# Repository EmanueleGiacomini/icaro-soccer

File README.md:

# Icaro Soccer
Questo repository contiene tutti i dati riguardo alla progettazione di hardware e software per i robot calciatori sviluppati nel corso **Icaro** tenuto nell'instituto tecnico industriale **Pacinotti-Archimede** di Roma.

## Struttura repository
Entrambe le sottocartelle di software e hardware contengono una cartella **_reference_** contenente ideè e link utili per la progettazione.
### Software
Ogni sottocartella è composta da un file di estensione **ino** che contiene il programma da inserire in Arduino, e da una cartella
**src** che contiene le librerie utilizzate dal programma.

Le librerie presenti sono:<p>
-**comlib** : libreria che gestisce la comunicazione fra i vari microcontrollori.<p>
-**motlib** : libreria che contiene algoritmi per i motori.<p>
-**sreglib** : libreria per la gestione dello _shift register_.<p>
-**strlib** : libreria per la manipolazione di stringhe.<p>
-**veclib** : liberia per la manipolazione di vettori e matrici.<p>

### Hardware
La sottocartella **drawings** contiene i disegni tecnici relativi alla struttura del robot.
**electronics** conterrà i disegni relativi ai circuiti stampati realizzati con EAGLE.

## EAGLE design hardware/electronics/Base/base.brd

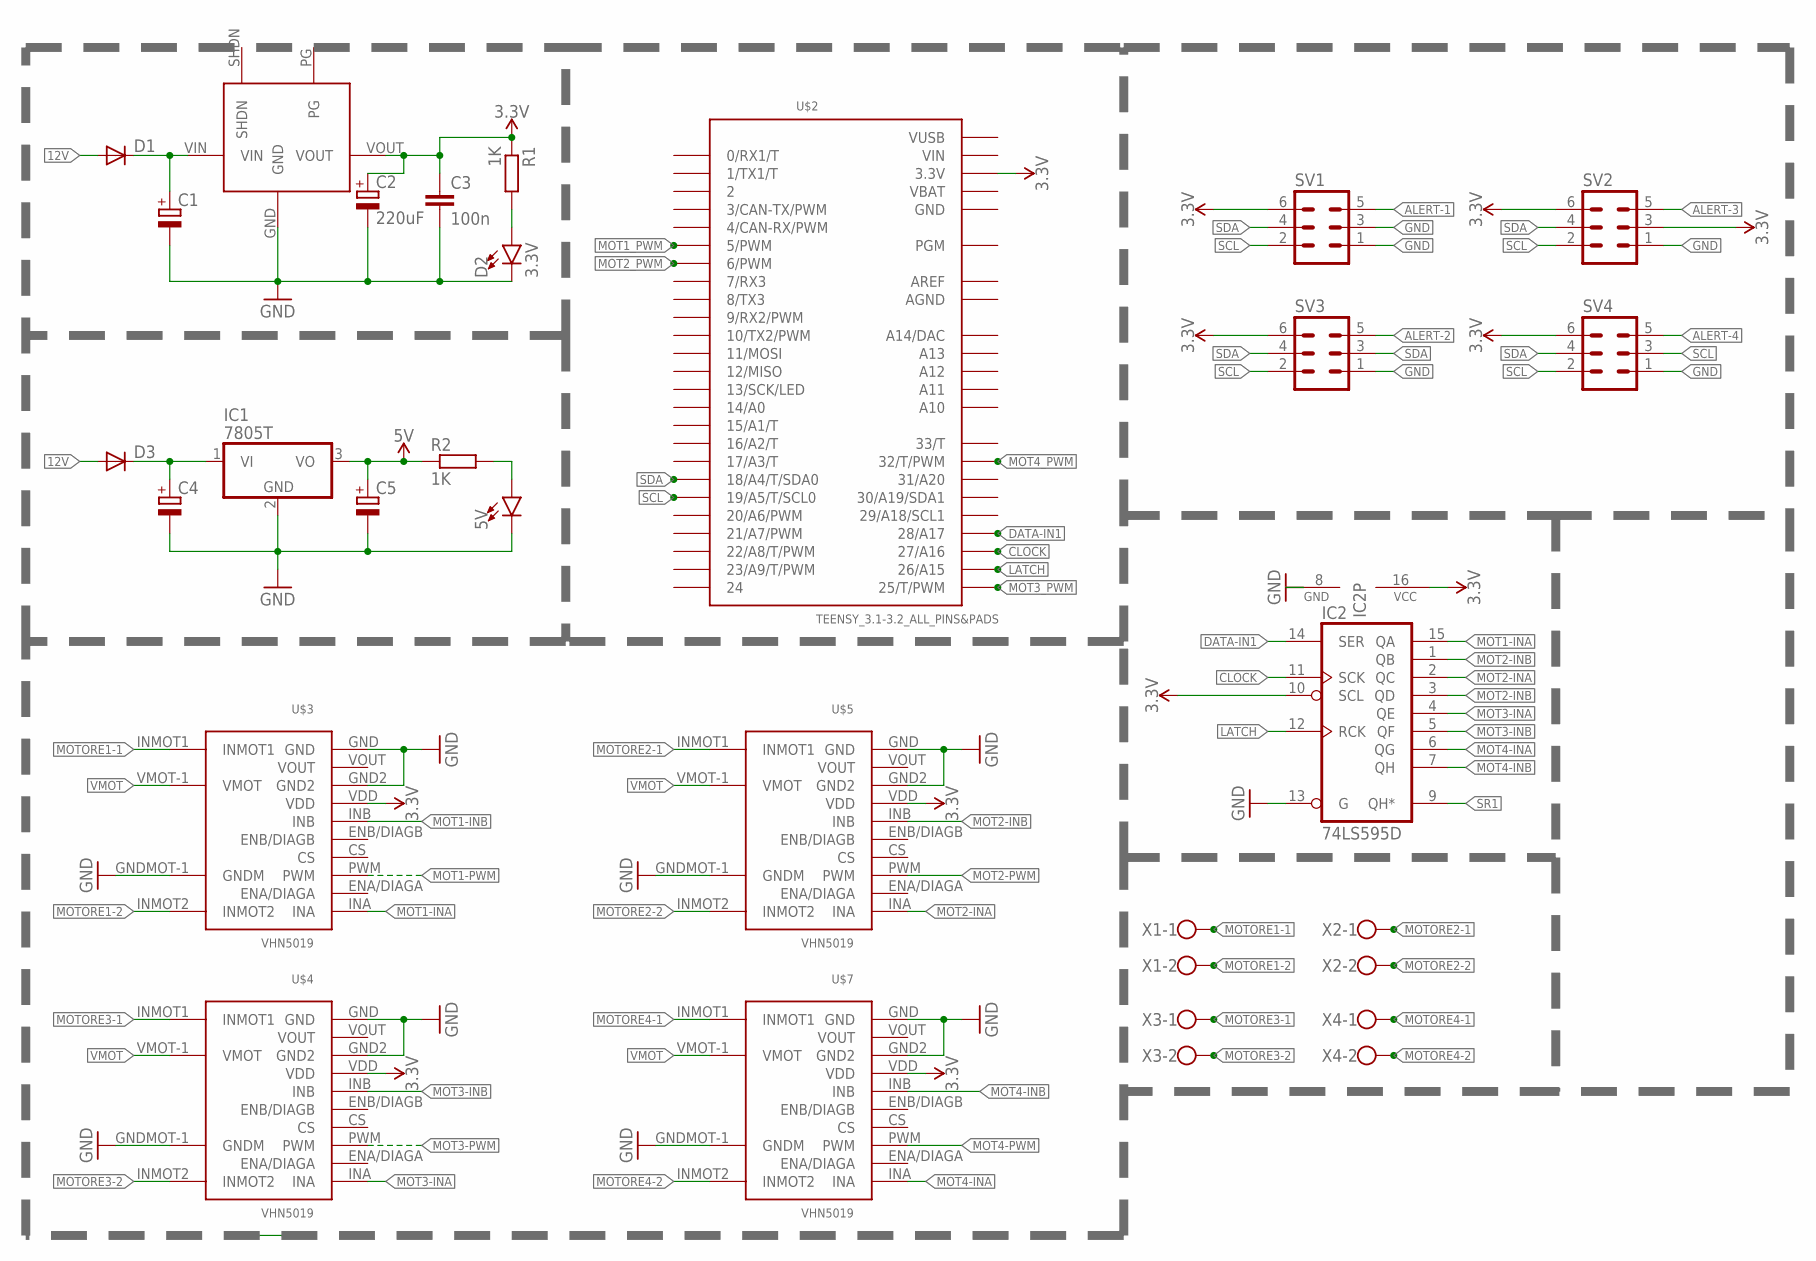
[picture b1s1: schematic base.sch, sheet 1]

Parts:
5V: LED-FKIT-1206; FKIT-LED-1206
C1, C4, C5: CPOL-EUE5-8.5; E5-8,5
C2: 220uF; E5-8,5
C3: 100n; C1206
D1, D3: DIODE-SMB; SMB
D2: 3.3V; FKIT-LED-1206
IC1: 7805T; TO220H
IC2: 74LS595D; SO16
R1, R2: 1K; M1206
SV1, SV2, SV3, SV4: MA03-2
U$2: TEENSY_3.1-3.2_ALL_PINS&PADS; TEENSY_3.0-3.2_ALL_PINS_&_PADS
U$3, U$4, U$5, U$7: VHN5019; MOTOR-SHIELD
U$6: REGOLATORE-3.3V-1A
X1, X2, X3, X4: W237-102

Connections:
3.3V: C2.+, C3.1, IC2.10 (SCL), IC2.16 (VCC), R1.1, SV1.6, SV2.3, SV2.6, SV3.6, SV4.6, U$2.3.3V, U$2.3.3V1 (3.3V), U$2.3.3V2 (3.3V), U$3.VDD, U$6.VOUT; also elsewhere on the board
5V: C5.+, IC1.3 (VO), R2.1
12V: D1.A, D3.A
AGND: U$2.AGND
ALERT-1: SV1.5
ALERT-2: SV3.5
ALERT-3: SV2.5
ALERT-4: SV4.5
AREF: U$2.AREF
CLOCK: IC2.11 (SCK), U$2.27 (27/A16); also elsewhere on the board
DATA-IN1: IC2.14 (SER), U$2.28 (28/A17)
GND: 5V.C, C1.-, C2.-, C3.2, C4.-, C5.-, D2.C, IC1.2 (GND), IC2.8 (GND), IC2.13 (G), SV1.1, SV1.3, SV2.1, SV3.1, SV4.1, U$2.GND, U$2.GND1 (GND), U$2.GND2 (GND), U$4.GND, U$4.GND2, U$4.GNDMOT-1 (GNDM), U$5.GND, U$5.GND2, U$5.GNDMOT-1 (GNDM), U$6.GND, U$7.GND, U$7.GND2, U$7.GNDMOT-1 (GNDM); also elsewhere on the board
GND2: U$3.GND, U$3.GND2
GNDM: U$3.GNDMOT-1 (GNDM)
LATCH: IC2.12 (RCK), U$2.26 (26/A15); also elsewhere on the board
MOT1-INA: IC2.15 (QA), U$3.INA
MOT1-INB: U$3.INB
MOT1-PWM: U$3.PWM
MOT1_PWM: U$2.5 (5/PWM)
MOT2-INA: IC2.2 (QC), U$5.INA
MOT2-INB: IC2.1 (QB), IC2.3 (QD), U$5.INB
MOT2-PWM: U$5.PWM
MOT2_PWM: U$2.6 (6/PWM)
MOT3-INA: IC2.4 (QE), U$4.INA
MOT3-INB: IC2.5 (QF), U$4.INB
MOT3-PWM: U$4.PWM
MOT3_PWM: U$2.25 (25/T/PWM)
MOT4-INA: IC2.6 (QG), U$7.INA
MOT4-INB: IC2.7 (QH), U$7.INB
MOT4-PWM: U$7.PWM
MOT4_PWM: U$2.32 (32/T/PWM)
MOTORE1-1: U$3.INMOT1, X1.1
MOTORE1-2: U$3.INMOT2, X1.2
MOTORE2-1: U$5.INMOT1, X2.1
MOTORE2-2: U$5.INMOT2, X2.2
MOTORE3-1: U$4.INMOT1, X3.1
MOTORE3-2: U$4.INMOT2, X3.2
MOTORE4-1: U$7.INMOT1, X4.1
MOTORE4-2: U$7.INMOT2, X4.2
unnamed: C1.+, D1.C, U$6.VIN
unnamed: D2.A, R1.2
unnamed: C4.+, D3.C, IC1.1 (VI)
unnamed: 5V.A, R2.2
SCL: SV1.2, SV2.2, SV3.2, SV4.2, SV4.3, U$2.19/A5 (19/A5/T/SCL0)
SDA: SV1.4, SV2.4, SV3.3, SV3.4, SV4.4, U$2.18/A4 (18/A4/T/SDA0)
SR1: IC2.9 (QH*); also elsewhere on the board
VBAT: U$2.VBAT
VDD: U$4.VDD, U$5.VDD, U$7.VDD
VIN: U$2.VIN
VMOT: U$3.VMOT-1 (VMOT), U$4.VMOT-1 (VMOT), U$5.VMOT-1 (VMOT), U$7.VMOT-1 (VMOT)
VUSB: U$2.VUSB

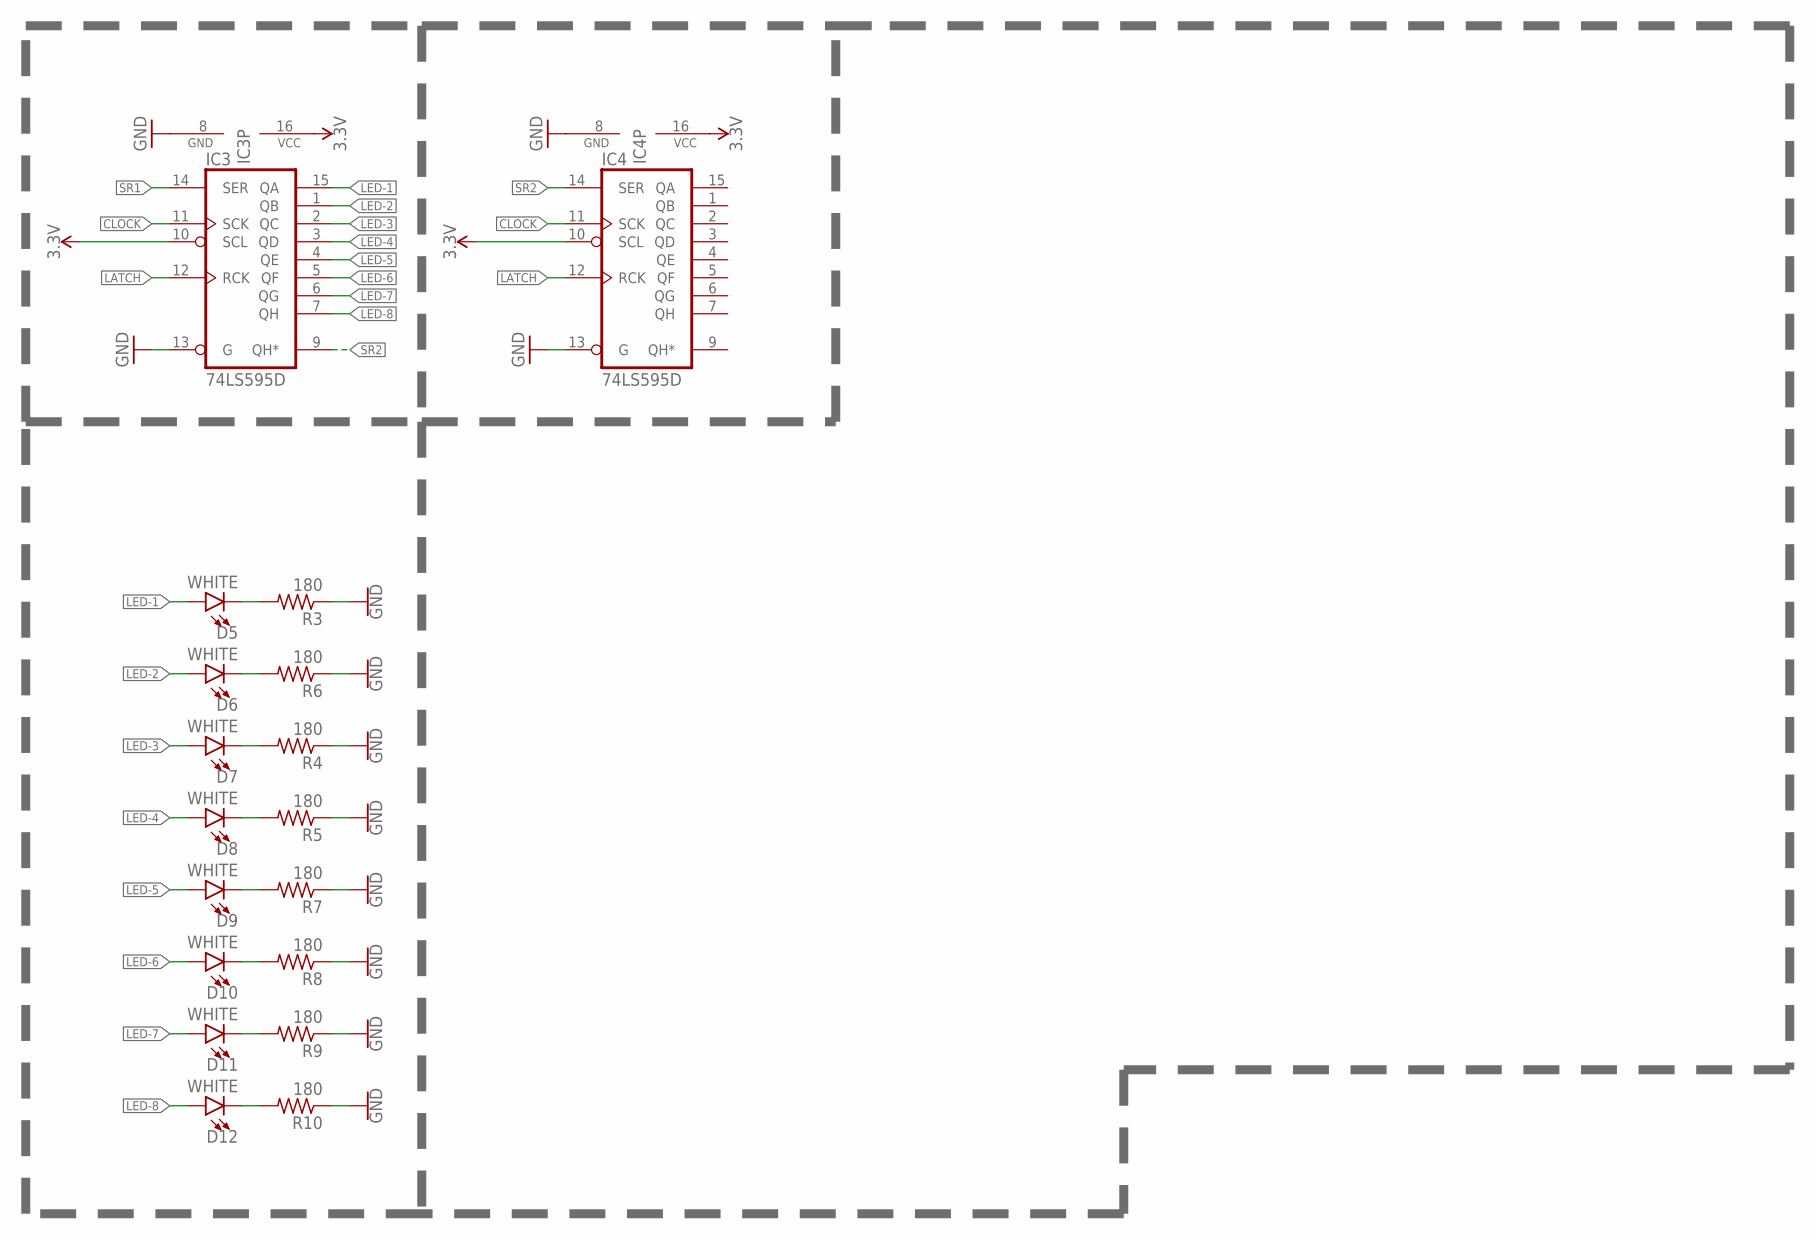
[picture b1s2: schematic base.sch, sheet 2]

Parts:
D5, D6, D7, D8, D9, D10, D11, D12: WHITE; LED-1206
IC3, IC4: 74LS595D; SO16
R3, R4, R5, R6, R7, R8, R9, R10: 180; 0204/7

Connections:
3.3V: IC3.10 (SCL), IC3.16 (VCC), IC4.10 (SCL), IC4.16 (VCC); also elsewhere on the board
CLOCK: IC3.11 (SCK), IC4.11 (SCK); also elsewhere on the board
GND: IC3.8 (GND), IC3.13 (G), IC4.8 (GND), IC4.13 (G), R3.1, R4.1, R5.1, R6.1, R7.1, R8.1, R9.1, R10.1; also elsewhere on the board
LATCH: IC3.12 (RCK), IC4.12 (RCK); also elsewhere on the board
LED-1: D5.A, IC3.15 (QA)
LED-2: D6.A, IC3.1 (QB)
LED-3: D7.A, IC3.2 (QC)
LED-4: D8.A, IC3.3 (QD)
LED-5: D9.A, IC3.4 (QE)
LED-6: D10.A, IC3.5 (QF)
LED-7: D11.A, IC3.6 (QG)
LED-8: D12.A, IC3.7 (QH)
unnamed: D5.C, R3.2
unnamed: D6.C, R6.2
unnamed: D7.C, R4.2
unnamed: D8.C, R5.2
unnamed: D9.C, R7.2
unnamed: D10.C, R8.2
unnamed: D11.C, R9.2
unnamed: D12.C, R10.2
SR1: IC3.14 (SER); also elsewhere on the board
SR2: IC3.9 (QH*), IC4.14 (SER)

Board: 2 copper layers, 45 parts (0 on the bottom side), 49 nets, no tracks yet.

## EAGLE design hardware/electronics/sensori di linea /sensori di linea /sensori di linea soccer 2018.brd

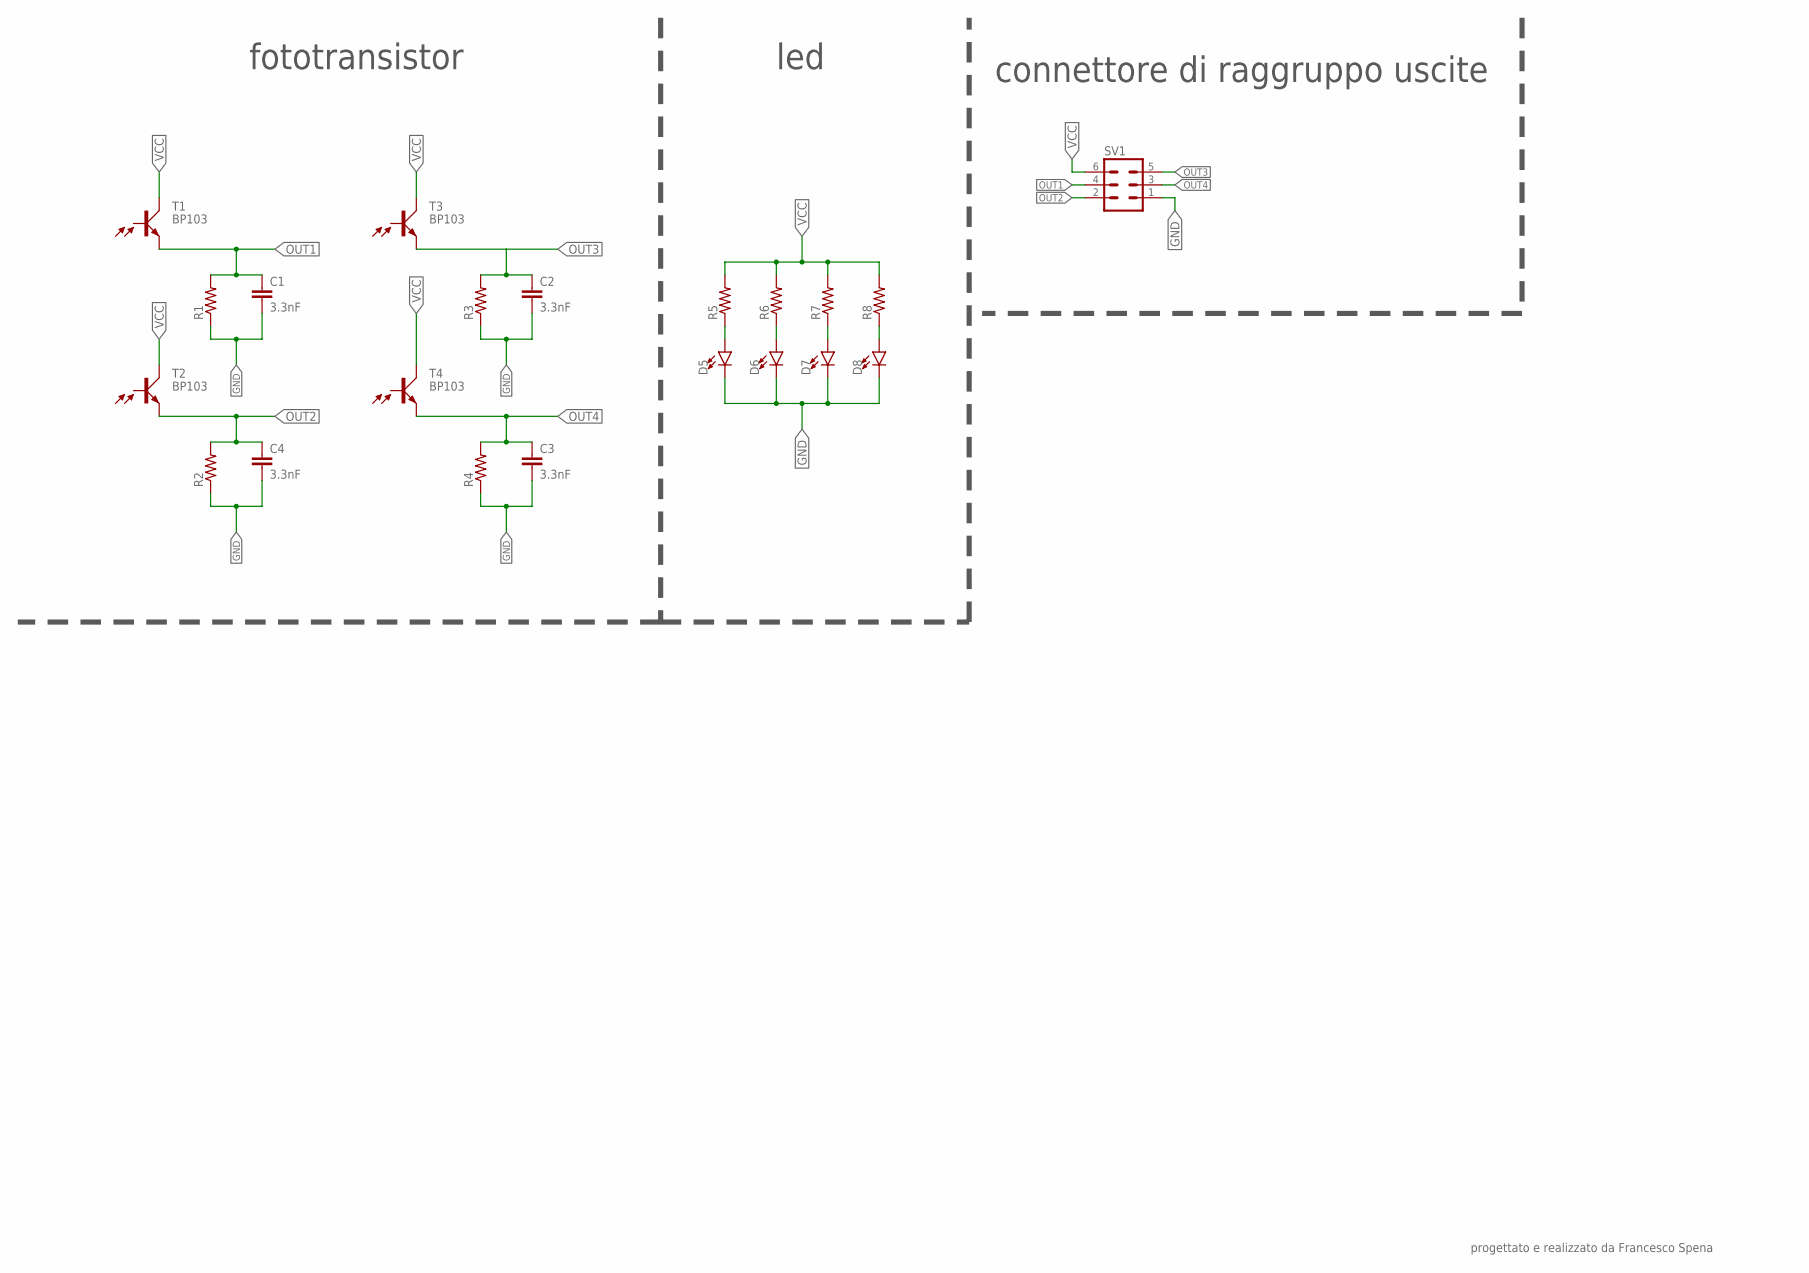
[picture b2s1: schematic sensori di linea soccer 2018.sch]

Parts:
C1, C2, C3, C4: 3.3nF; 0603
D5, D6, D7, D8: LED3MM; LED_3MM
R1, R2, R3, R4, R5, R6, R7, R8: R-US_0204/7; 0204/7
SV1: MA03-2
T1, T2, T3, T4: BP103

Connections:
GND: C1.2, C2.2, C3.2, C4.2, D5.K (C), D6.K (C), D7.K (C), D8.K (C), R1.1, R2.1, R3.1, R4.1, SV1.1
unnamed: D5.A, R5.1
unnamed: D6.A, R6.1
unnamed: D7.A, R7.1
unnamed: D8.A, R8.1
OUT1: C1.1, R1.2, SV1.4, T1.E
OUT2: C4.1, R2.2, SV1.2, T2.E
OUT3: C2.1, R3.2, SV1.5, T3.E
OUT4: C3.1, R4.2, SV1.3, T4.E
VCC: R5.2, R6.2, R7.2, R8.2, SV1.6, T1.C, T2.C, T3.C, T4.C

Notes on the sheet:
fototransistor
led
connettore di raggruppo uscite
progettato e realizzato da Francesco Spena

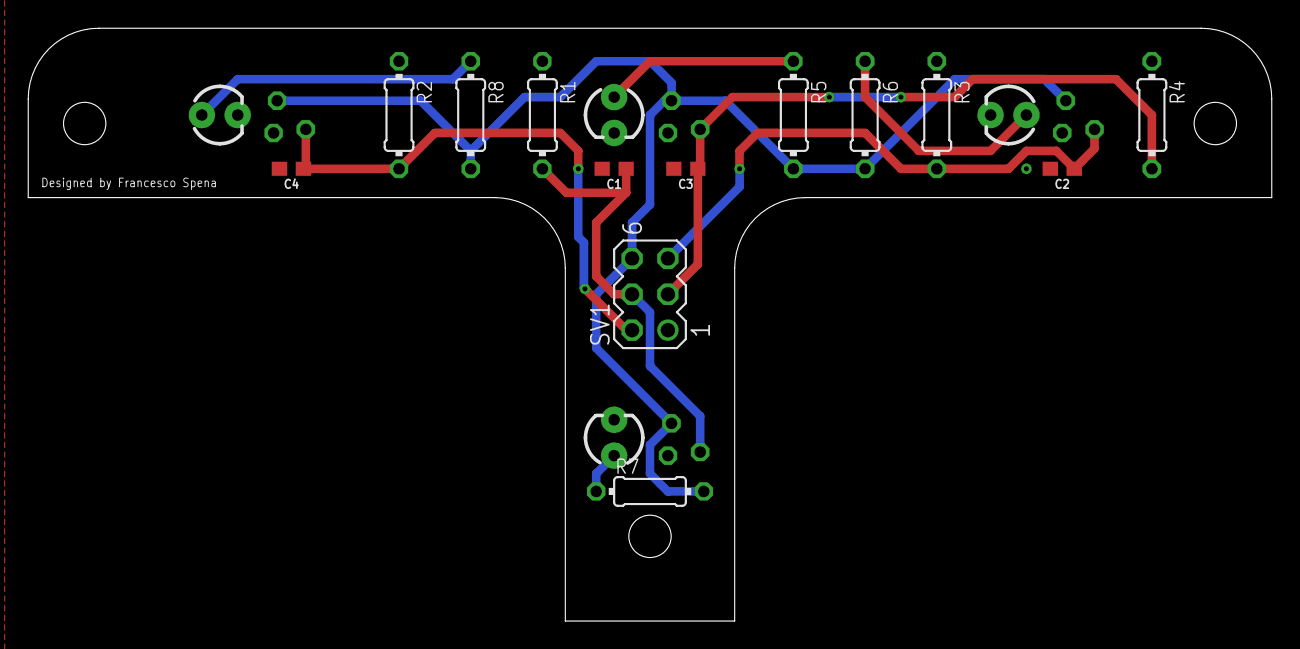
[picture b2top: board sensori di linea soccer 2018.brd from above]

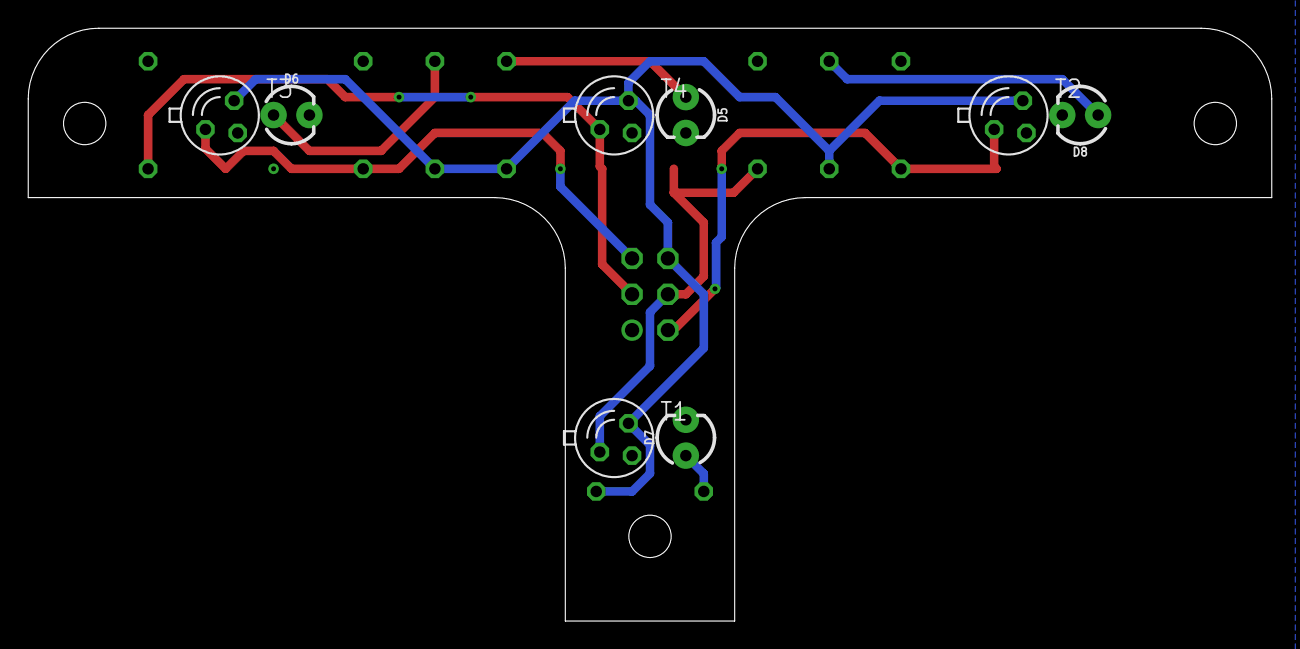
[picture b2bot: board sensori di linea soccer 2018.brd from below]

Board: 2 copper layers, 88.1 x 42.0 mm, 21 parts (8 on the bottom side), 10 nets.

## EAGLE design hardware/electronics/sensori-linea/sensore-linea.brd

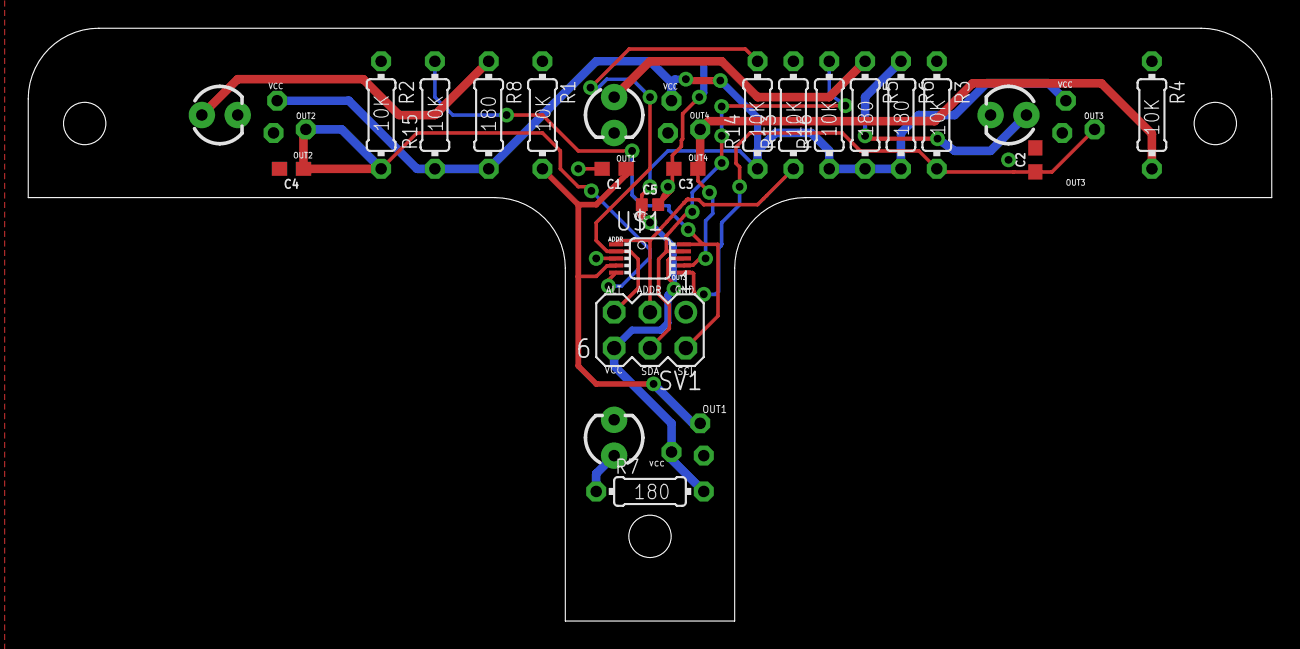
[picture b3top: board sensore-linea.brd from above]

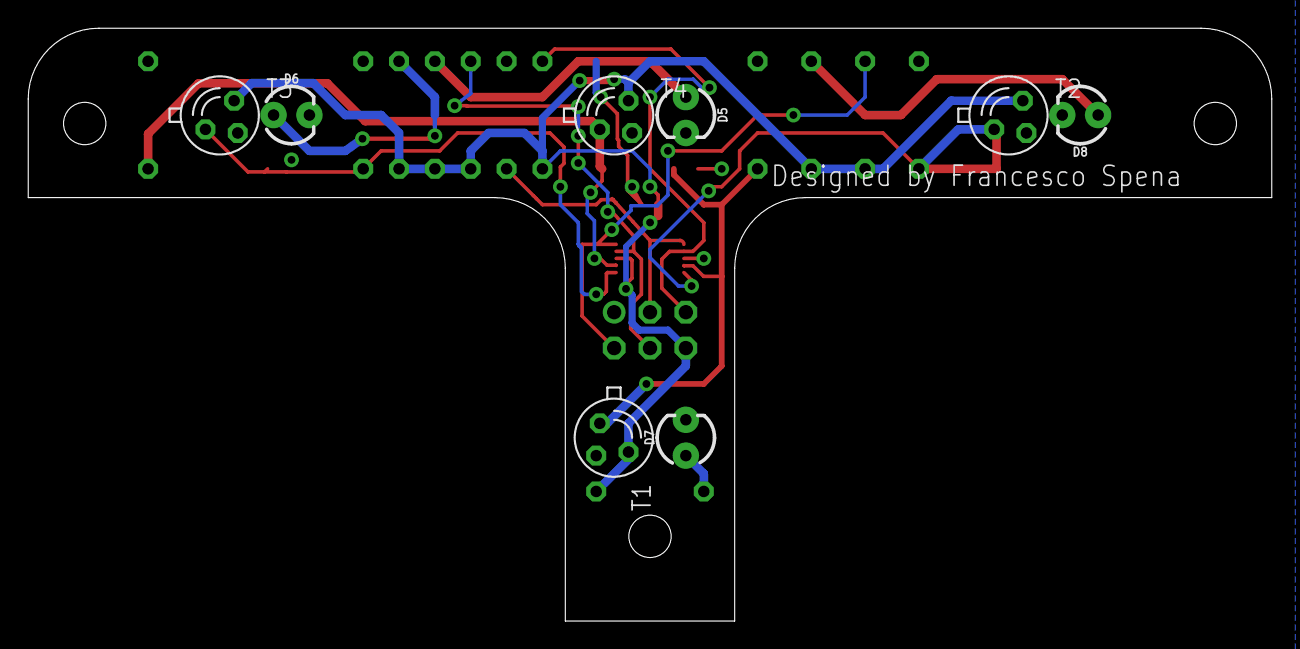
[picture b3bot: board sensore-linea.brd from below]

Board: 2 copper layers, 88.1 x 42.0 mm, 27 parts (8 on the bottom side), 14 nets.

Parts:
C1, C2, C3, C4: 3.3nF; 0603
C5: 1.0uF; 0402
D5, D6, D7, D8: LED_3MM
R1, R2, R3, R4, R13, R14, R15, R16: 10K; 0204/7
R5, R6, R7: 180; 0204/7
R8: 0204/7
SV1: MA03-2
T1, T2, T3, T4: BP103
U$1: ADS1015IDGT; MSOP10_0.5

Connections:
ADDR: R13.1, SV1.3, U$1.1
ALERT: R14.2, SV1.5, U$1.2
GND: C1.2, C2.2, C3.2, C4.2, C5.2, D5.K, D6.K, D7.K, D8.K, R1.1, R2.1, R3.1, R4.1, R13.2, SV1.1, U$1.3
unnamed: D5.A, R5.1
unnamed: D6.A, R6.1
unnamed: D7.A, R7.1
unnamed: D8.A, R8.1
OUT1: C1.1, R1.2, T1.E, U$1.4
OUT2: C4.1, R2.2, T2.E, U$1.5
OUT3: C2.1, R3.2, T3.E, U$1.6
OUT4: C3.1, R4.2, T4.E, U$1.7
SCL: R15.2, SV1.2, U$1.10
SDA: R16.2, SV1.4, U$1.9
VCC: C5.1, R5.2, R6.2, R7.2, R8.2, R14.1, R15.1, R16.1, SV1.6, T1.C, T2.C, T3.C, T4.C, U$1.8

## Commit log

2017-12-28 -Add comlib.h/cpp -Add motlib.h/cpp -Add sreg.h/cpp -Add strlib.h/cpp -Add veclib.h/cpp
2017-12-28 -Add Holonomic drive ref
2017-12-28 modifiche
2017-12-28 Dump to load new folders
2017-12-29 Auto stash before merge of "master" and "origin/master"
2017-12-29 Nuovi componenti
2018-01-10 Rimozione cartelle locali per consentire l'accesso libero fra le librerie
2018-01-10 Add comments
2018-01-10 dimensioni motori
2018-01-11 prova
2018-01-11 materiale motori
2018-01-11 link
2018-01-11 rimosso prova
2018-01-11 Ripristinato commit 185509
    Causa impossibile pullare 89a5d01eacee82af45c838ab3aca35117d57fd0a
2018-01-11 rimossi link
2018-01-11 aggiunta base motori
2018-01-12 Risolto problema .DS_Store
2018-01-12 Aggiunto materiale extra da calciatore-2015-16
    Pcb della scheda inferiore, superiore e dei sensori di linea
2018-01-12 modifiche e correzioni
2018-01-16 Aggiunta Libreria Sparkfun Eagle
2018-01-16 aggiunte a base motori
2018-01-16 nuovi sensori di linea 2018
2018-01-17 file board sensori di linea 2018
2018-01-17 modifiche a sensori di linea 2018
2018-01-18 Aggiorno veclib
2018-01-18 librerie sparkfun
2018-01-18 base aggiornata
2018-01-18 modfiche
2018-01-18 librerie teensy 3.2
2018-01-18 problema librerie
2018-01-18 librerie
2018-01-18 sensori di linea anteriore 2018
2018-01-18 aggiornamento base
2018-01-18 miglioramenti sensori di linea 2018
2018-01-18 eliminazione sensori di linea anteriori
    li ho eliminati perchè prima avevamo i sensori di linea anteriori con una forma diversa ora invece sono tutti uguali
2018-01-18 sensori di linea eliminati
2018-01-18 pololu vnh5019(data sheeet,dimension diagram)
2018-01-19 modifica a base motori definitiva
2018-01-20 Aggiunte librerie-fabio per EAGLE
2018-01-20 Prova-OOP
    Programma di prova per programmazione orientata agli oggetti
2018-01-21 spostamenti
2018-01-22 Sensori di linea 2018
2018-01-22 aggiornamenti sensori
2018-01-23 base
2018-01-23 modiche 2
2018-01-23 aggiunta fie sensori di linea nuovi
2018-01-24 sensori di linea completi 2018
2018-01-24 zip e regole per eagle
2018-01-25 sensori di linea 2018 zip
2018-01-25 sensori di linea senza dxf
2018-01-26 eliminazti sensori di linea 2
2018-01-26 Aggiunto file "da-aggiungere.txt" e modificato .gitignore
2018-01-30 SENZA DXF
2018-01-30 modifica nome cartella
2018-01-30 Aggiunti sensori-linea
2018-01-30 Fix sensore-linea + zip per pcbway
2018-01-30 zip sensori di linea
2018-01-30 aggiornamenti
2018-01-30 aggiornamenti 2
2018-02-06 aggiornamenti base
2018-02-07 Modifica cartelle libreria
2018-02-07 schematico prototipo
2018-02-07 schema base piu lbr
2018-02-07 Fix problema di pull
    Causa probabile: spazi nel nome dei file/cartelle:
2018-02-07 Aggiunto schema-prototipo, fix minori
    fix minori: spostata cartella vhn5019 da hardware/electronics ad hardware/reference/motor-driver
2018-02-07 aggiunta modifiche apportate alle librerie
2018-02-08 Libreria modificata
2018-02-08 modifiche schematico prototipo
2018-02-09 Fix base.sch, base.brd
2018-02-09 Rimossi backup .b#n
    Sono fastidiosi :)
2018-02-10 aggiunta step-down
2018-02-11 aggiunta bussola
2018-02-13 tutto
2018-02-14 Fixed base schematic and board
2018-02-14 Rimossi .b#n (dinuovo)
    Valerio togli la spunta ad Amend please :)
2018-02-20 regolamento
2018-02-21 base+
2018-02-21 Rimozione regolamento
    Causa errore nel pull del repository
2018-02-22 Aggiornata libreria motori
2018-02-25 Aggiornamento lib-motori
2018-03-04 Aggiunta inutile
2018-03-04 Collegate le linee alla basa
2018-03-09 bussola
2018-03-09 prova.motori
2018-03-15 Robot
2018-03-15 Sliena
2018-03-22 Slinea
2018-03-22 Aggiunte librerie linelib, robot.
    In oltre e' stata inserita come reference la mia tesina
2018-03-23 Aggiunte librerie esterne
2018-03-23 small-fix :)
2018-03-24 Small fixes to libraries
2018-03-27 Sliena modifica
    @EmanueleGiacomini ora va bene?
2018-04-05 LineSensor&LineHandler
2018-04-05 Aggiornamento SLinea1
2018-04-05 Auto stash before merge of "master" and "origin/master"
    modifiche LineHandler
2018-04-06 Update Slinea1.ino
    Aggiunti vari commenti
2018-04-06 getTTL
2018-04-06 Reset
2018-04-07 Aggiornate librerie
2018-04-08 Aggiunta pixytracker lib
2018-04-08 Little update
2018-04-08 aggiunta libreria pixy
2018-04-11 Aggiunti programmi 2015-16
2018-04-11 Aggiornata pixytracker
2018-04-11 modifiche libreria pixytraker
2018-04-11 Aggiunta phoeniximu e phoenixrobot
2018-04-14 risoluzione problemi phoeniximu
2018-04-15 Aggiornato phoeniximu, phoenixrobot, software.ino
2018-04-16 Aggiornato pid pixy, imu
2018-04-17 Aggiornamenti minori software
2018-04-18 Added teensy-firmware and orazio project
2018-07-31 Added reference 2015 project
2018-11-07 niente
2018-12-28 sensori di linea

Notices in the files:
parts and their libraries:
SparkFun-LED: Licensing: Creative Commons ShareAlike 4.0 International - https://creativecommons.org/licenses/by-sa/4.0
